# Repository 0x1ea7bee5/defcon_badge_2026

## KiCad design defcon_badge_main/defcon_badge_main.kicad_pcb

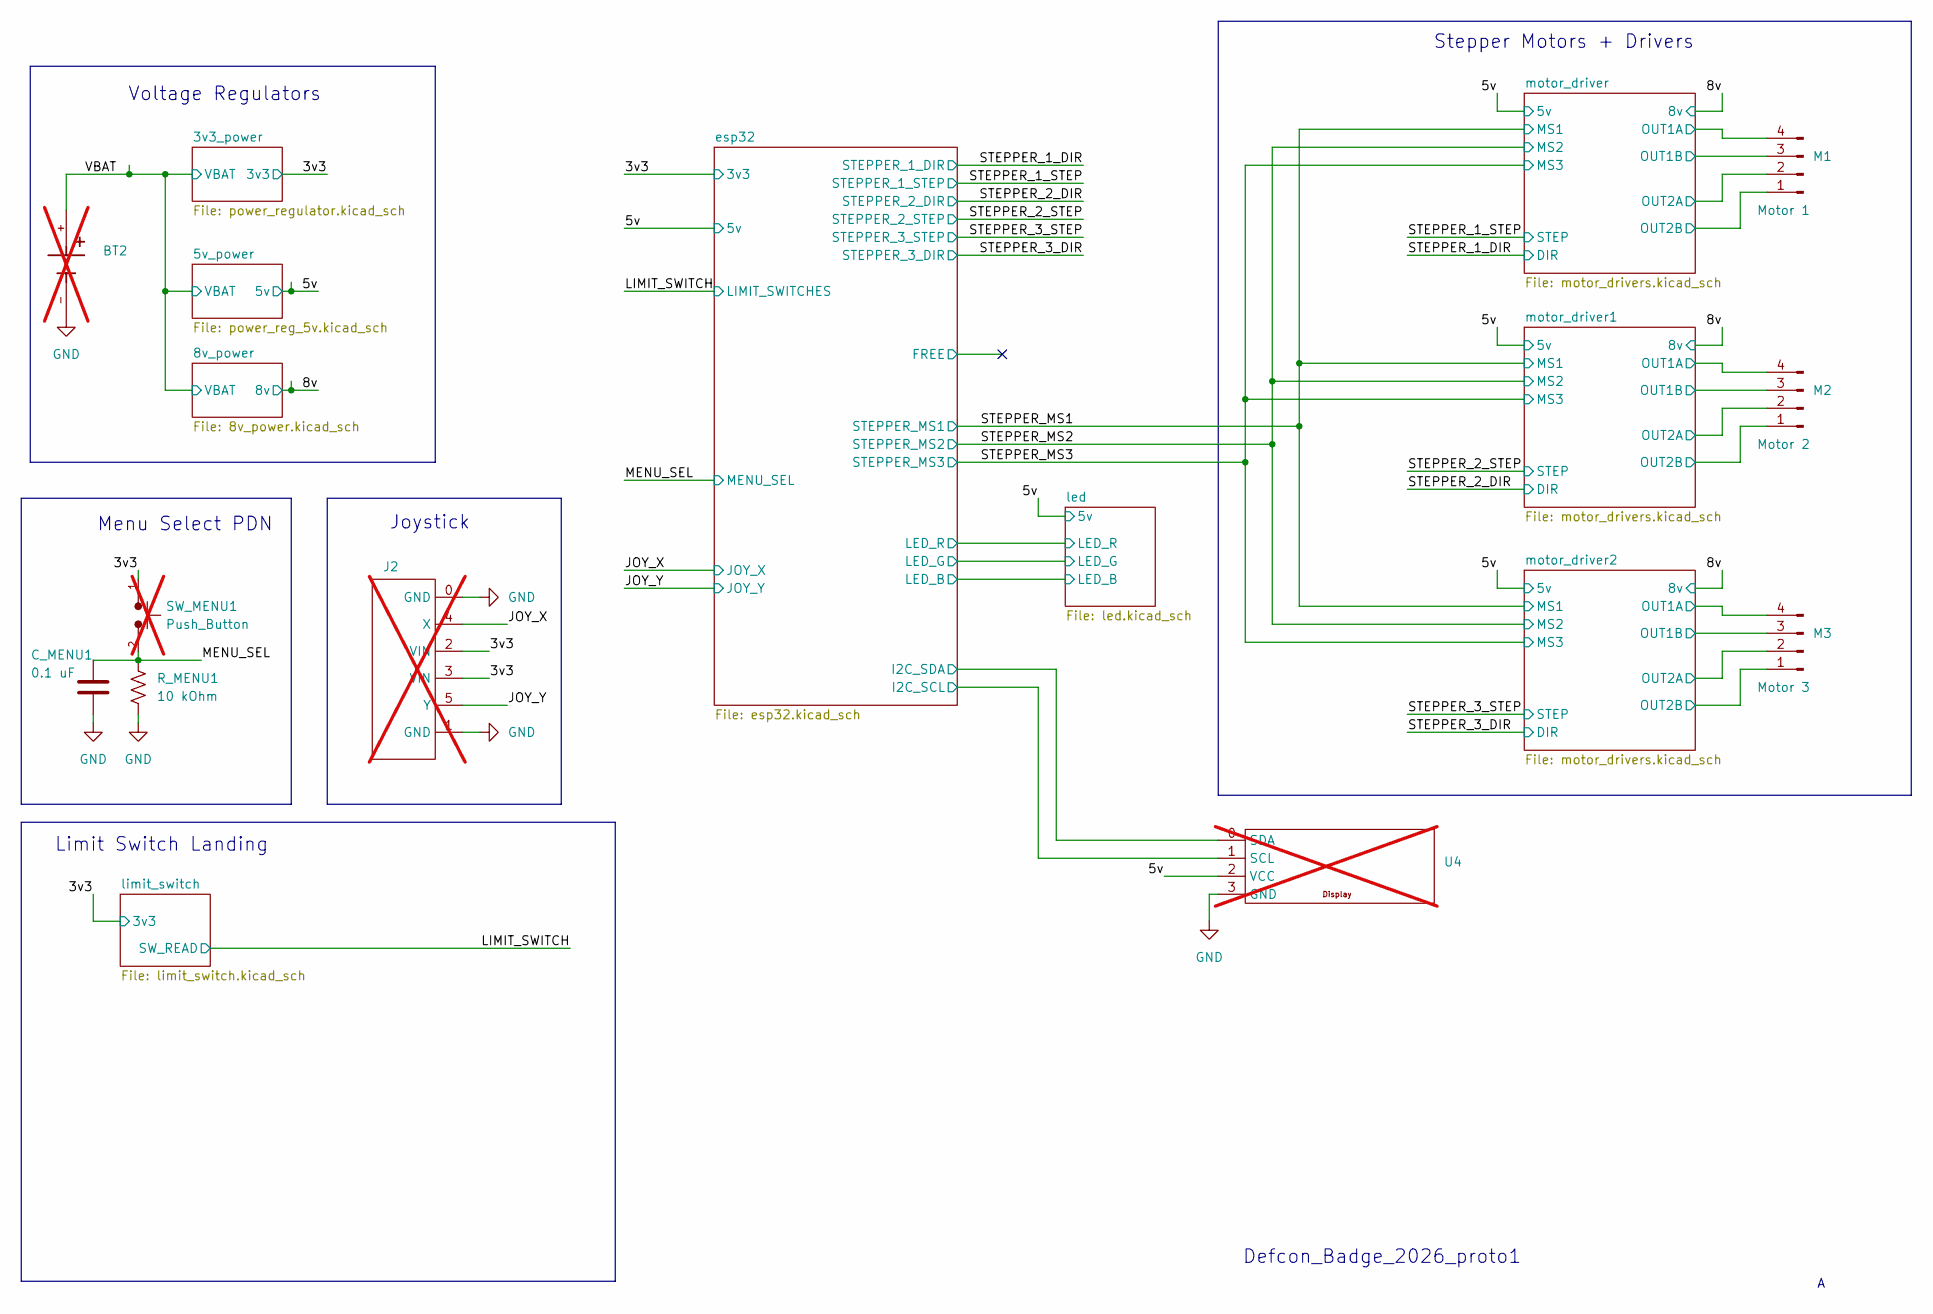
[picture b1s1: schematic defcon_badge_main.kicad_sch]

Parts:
BT2: BK-18650-PC2; BAT_BK-18650-PC2; PARTREV F; not fitted
C_MENU1: 0.1 uF; R_0402_1005Metric_Pad0.72x0.64mm_HandSolder_MINE; Rating 16V; MPN GMC10X7R104M16NTD
J2: joystick; not fitted
M1: Motor 1; motor_pins
M2: Motor 2; motor_pins
M3: Motor 3; motor_pins
R_MENU1: 10 kOhm; R_0805_2012Metric_Pad1.20x1.40mm_HandSolder_MINE; MPN RM10F1002CT
SW_MENU1: Push_Button; SW_SPST_PTS645; not fitted
U4: display; not fitted

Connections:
/3v3: J2.2 (VIN), J2.3 (VIN), SW_MENU1.1; also elsewhere on the board
/5v: U4.2 (VCC); also elsewhere on the board
/JOY_X: J2.4 (X); also elsewhere on the board
/JOY_Y: J2.5 (Y); also elsewhere on the board
/MENU_SEL: C_MENU1.2, R_MENU1.1, SW_MENU1.2; also elsewhere on the board
/VBAT: BT2.+; also elsewhere on the board
/esp32/I2C_SCL: U4.1 (SCL); also elsewhere on the board
/esp32/I2C_SDA: U4.0 (SDA); also elsewhere on the board
/motor_driver1/OUT1A: M2.4; also elsewhere on the board
/motor_driver1/OUT1B: M2.3; also elsewhere on the board
/motor_driver1/OUT2A: M2.2; also elsewhere on the board
/motor_driver1/OUT2B: M2.1; also elsewhere on the board
/motor_driver2/OUT1A: M3.4; also elsewhere on the board
/motor_driver2/OUT1B: M3.3; also elsewhere on the board
/motor_driver2/OUT2A: M3.2; also elsewhere on the board
/motor_driver2/OUT2B: M3.1; also elsewhere on the board
/motor_driver/OUT1A: M1.4; also elsewhere on the board
/motor_driver/OUT1B: M1.3; also elsewhere on the board
/motor_driver/OUT2A: M1.2; also elsewhere on the board
/motor_driver/OUT2B: M1.1; also elsewhere on the board
GND: BT2.-, C_MENU1.1, J2.0 (GND), J2.1 (GND), R_MENU1.2, U4.3 (GND); also elsewhere on the board

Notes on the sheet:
Stepper Motors + Drivers
Defcon_Badge_2026_proto1
Voltage Regulators
Joystick
Menu Select PDN
Limit Switch Landing

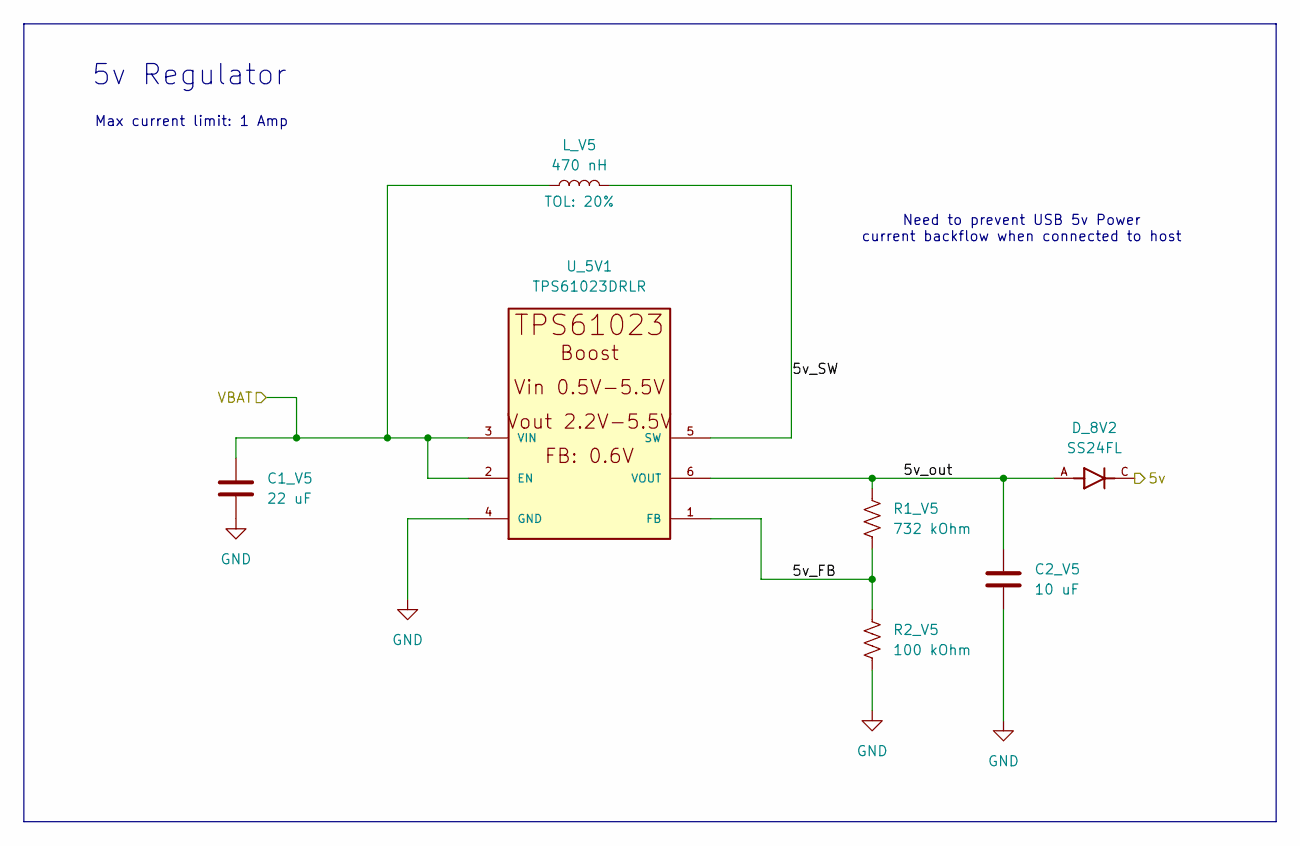
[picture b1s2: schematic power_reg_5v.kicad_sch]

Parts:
C1_V5: 22 uF; R_0805_2012Metric_Pad1.20x1.40mm_HandSolder_MINE; Rating 16V; MPN GMC21X5R226K16NT
C2_V5: 10 uF; R_0805_2012Metric_Pad1.20x1.40mm_HandSolder_MINE; Rating 16V; MPN GMC21X5R106K16NT
D_8V2: SS24FL; SODFL3617X108N; PARTREV A
L_V5: 470 nH; L_Neosid_SMS-ME3010; MPN 74479288147
R1_V5: 732 kOhm; R_1206_3216Metric_Pad1.30x1.75mm_HandSolder_MINE; MPN RM12F7323CT
R2_V5: 100 kOhm; R_1206_3216Metric_Pad1.30x1.75mm_HandSolder_MINE; MPN RM12F1003CT
U_5V1: TPS61023DRLR; SOT563-ORI; MPN TPS61023DRLR

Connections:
/5v: D_8V2.C; also elsewhere on the board
/5v_power/5v_FB: R1_V5.2, R2_V5.1, U_5V1.1 (FB)
/5v_power/5v_SW: L_V5.2, U_5V1.5 (SW)
/5v_power/5v_out: C2_V5.1, D_8V2.A, R1_V5.1, U_5V1.6 (VOUT)
/VBAT: C1_V5.1, L_V5.1, U_5V1.2 (EN), U_5V1.3 (VIN); also elsewhere on the board
GND: C1_V5.2, C2_V5.2, R2_V5.2, U_5V1.4 (GND); also elsewhere on the board

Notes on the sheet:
Max current limit: 1 Amp
Need to prevent USB 5v Power current backflow when connected to host
5v Regulator

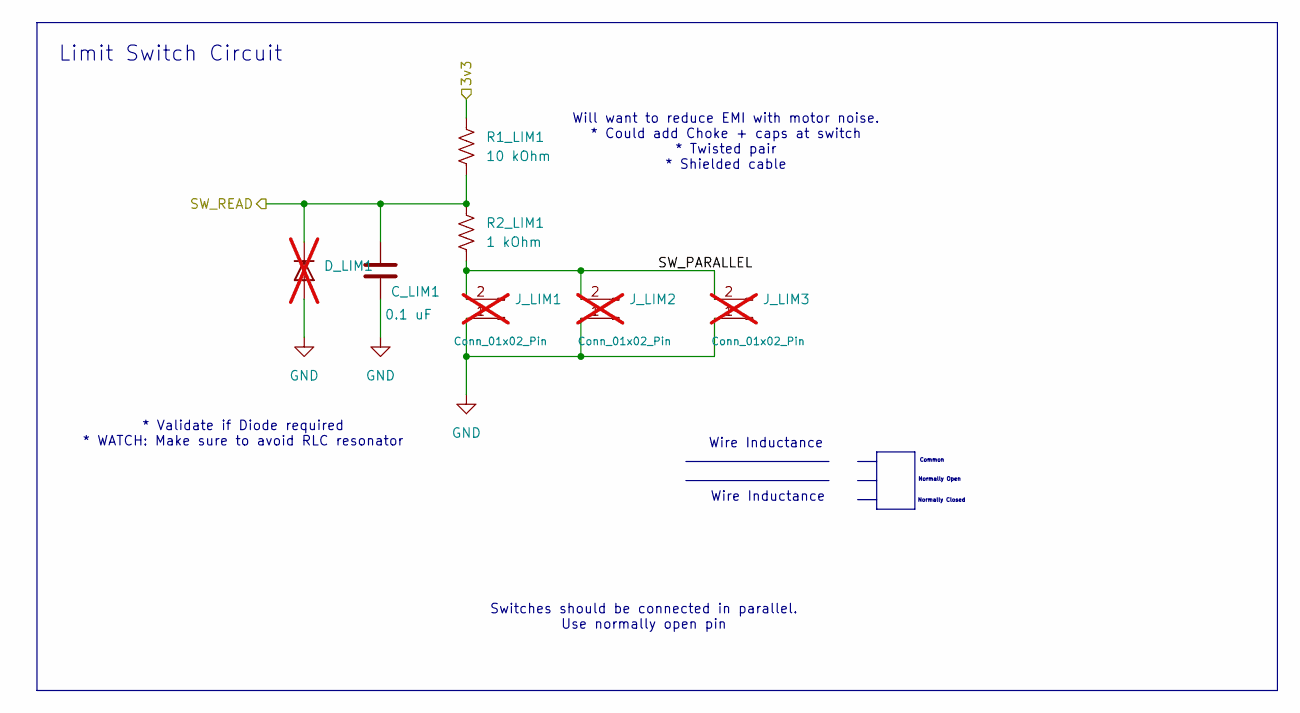
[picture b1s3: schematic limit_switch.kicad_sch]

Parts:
C_LIM1: 0.1 uF; R_0603_1608Metric_Pad0.98x0.95mm_HandSolder_MINE; Rating 16V; MPN GMC10X7R104M16NTD
D_LIM1: SOD-123; MPN 1N4148W-TP; not fitted
J_LIM1, J_LIM2, J_LIM3: Conn_01x02_Pin; pad_limit_switch; not fitted
R1_LIM1: 10 kOhm; R_0805_2012Metric_Pad1.20x1.40mm_HandSolder_MINE; MPN RM10F1002CT
R2_LIM1: 1 kOhm; R_1206_3216Metric_Pad1.30x1.75mm_HandSolder_MINE; MPN RMCS1206JT1K00

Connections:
/3v3: R1_LIM1.1; also elsewhere on the board
/LIMIT_SWITCH: C_LIM1.2, D_LIM1.1 (K), R1_LIM1.2, R2_LIM1.1; also elsewhere on the board
/limit_switch/SW_PARALLEL: J_LIM1.2, J_LIM2.2, J_LIM3.2, R2_LIM1.2
GND: C_LIM1.1, D_LIM1.2 (A), J_LIM1.1, J_LIM2.1, J_LIM3.1; also elsewhere on the board

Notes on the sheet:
* Validate if Diode required * WATCH: Make sure to avoid RLC resonator
Wire Inductance
Common
Normally Closed
Will want to reduce EMI with motor noise. * Could add Choke + caps at switch * Twisted pair * Shielded cable
Switches should be connected in parallel. Use normally open pin
Normally Open
Limit Switch Circuit

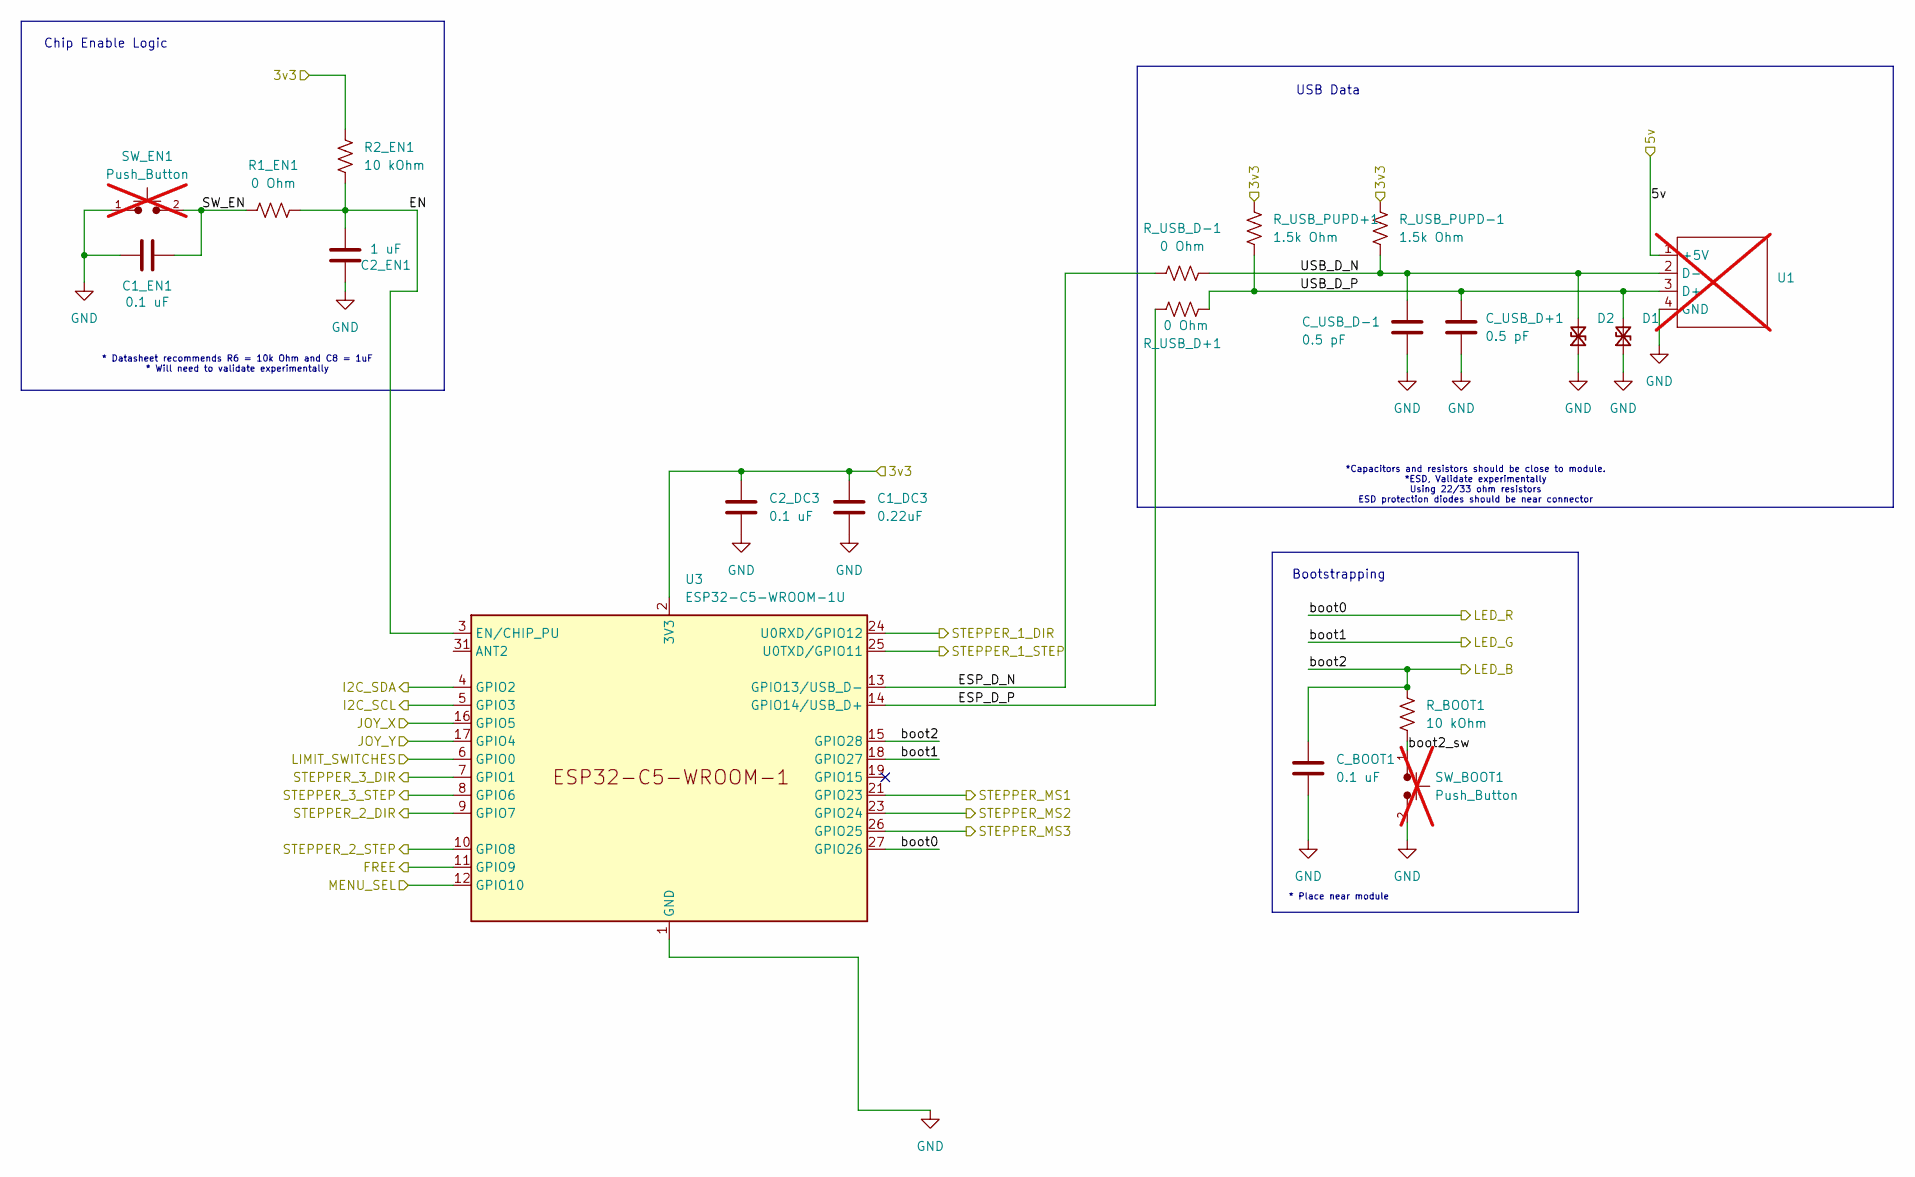
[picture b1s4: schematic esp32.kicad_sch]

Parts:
C1_DC3: 0.22uF; R_0805_2012Metric_Pad1.20x1.40mm_HandSolder_MINE; Rating 16V; MPN GMC10X5R224K25NT
C1_EN1, C2_DC3: 0.1 uF; R_0603_1608Metric_Pad0.98x0.95mm_HandSolder_MINE; Rating 16V; MPN GMC10X7R104M16NTD
C2_EN1: 1 uF; R_0805_2012Metric_Pad1.20x1.40mm_HandSolder_MINE; MPN GMC21X5R105K16NT
C_BOOT1: 0.1 uF; R_0603_1608Metric_Pad0.98x0.95mm_HandSolder_MINE; Rating 16V; MPN GMC10X7R104M16NTD
C_USB_D+1: 0.5 pF; R_0402_1005Metric_Pad0.72x0.64mm_HandSolder_MINE; Rating 16V; MPN GMC04CG0R5C50NT
C_USB_D-1: 0.5 pF; R_0402_1005Metric_Pad0.72x0.64mm_HandSolder_MINE; Rating 16V; MPN GMC04CG0R5C50NT
D1, D2: PESD0402; R_0402_1005Metric_Pad0.72x0.64mm_HandSolder_MINE; Rating 14VWM/40VC; MPN CES10402V05B0DG
R1_EN1: 0 Ohm; R_0603_1608Metric_Pad0.98x0.95mm_HandSolder_MINE; MPN RM06J000CT
R2_EN1: 10 kOhm; R_0805_2012Metric_Pad1.20x1.40mm_HandSolder_MINE; MPN RM10F1002CT
R_BOOT1: 10 kOhm; R_0805_2012Metric_Pad1.20x1.40mm_HandSolder_MINE; MPN RM10F1002CT
R_USB_D+1: 0 Ohm; R_0402_1005Metric_Pad0.72x0.64mm_HandSolder_MINE; MPN RM04J000CT
R_USB_D-1: 0 Ohm; R_0402_1005Metric_Pad0.72x0.64mm_HandSolder_MINE; MPN RM04J000CT
R_USB_PUPD+1: 1.5k Ohm; R_0402_1005Metric_Pad0.72x0.64mm_HandSolder_MINE; MPN RM04J152CT
R_USB_PUPD-1: 1.5k Ohm; R_0402_1005Metric_Pad0.72x0.64mm_HandSolder_MINE; MPN RM04J152CT
SW_BOOT1: Push_Button; SW_SPST_PTS810; not fitted
SW_EN1: Push_Button; SW_SPST_PTS810; not fitted
U1: usb_typea_boardedge; not fitted
U3: ESP32-C5-WROOM-1U; MPN ESP32-C5-WROOM-1U-N8R8

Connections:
/3v3: C1_DC3.1, C2_DC3.1, R2_EN1.2, R_USB_PUPD+1.2, R_USB_PUPD-1.2, U3.2 (3V3); also elsewhere on the board
/5v: U1.1 (+5V); also elsewhere on the board
/JOY_X: U3.16 (GPIO5); also elsewhere on the board
/JOY_Y: U3.17 (GPIO4); also elsewhere on the board
/LIMIT_SWITCH: U3.6 (GPIO0); also elsewhere on the board
/MENU_SEL: U3.12 (GPIO10); also elsewhere on the board
/STEPPER_1_DIR: U3.24 (U0RXD/GPIO12); also elsewhere on the board
/STEPPER_1_STEP: U3.25 (U0TXD/GPIO11); also elsewhere on the board
/STEPPER_2_DIR: U3.9 (GPIO7); also elsewhere on the board
/STEPPER_2_STEP: U3.10 (GPIO8); also elsewhere on the board
/STEPPER_3_DIR: U3.7 (GPIO1); also elsewhere on the board
/STEPPER_3_STEP: U3.8 (GPIO6); also elsewhere on the board
/STEPPER_MS1: U3.21 (GPIO23); also elsewhere on the board
/STEPPER_MS2: U3.23 (GPIO24); also elsewhere on the board
/STEPPER_MS3: U3.26 (GPIO25); also elsewhere on the board
/esp32/EN: C2_EN1.1, R1_EN1.2, R2_EN1.1, U3.3 (EN/CHIP_PU)
/esp32/ESP_D_N: R_USB_D-1.1, U3.13 (GPIO13/USB_D-)
/esp32/ESP_D_P: R_USB_D+1.2, U3.14 (GPIO14/USB_D+)
/esp32/FREE: U3.11 (GPIO9)
/esp32/I2C_SCL: U3.5 (GPIO3); also elsewhere on the board
/esp32/I2C_SDA: U3.4 (GPIO2); also elsewhere on the board
/esp32/SW_EN: C1_EN1.1, R1_EN1.1, SW_EN1.2
/esp32/USB_D_N: C_USB_D-1.1, D2.2 (A2), R_USB_D-1.2, R_USB_PUPD-1.1, U1.2 (D-)
/esp32/USB_D_P: C_USB_D+1.1, D1.2 (A2), R_USB_D+1.1, R_USB_PUPD+1.1, U1.3 (D+)
/esp32/boot0: U3.27 (GPIO26); also elsewhere on the board
/esp32/boot1: U3.18 (GPIO27); also elsewhere on the board
/esp32/boot2: C_BOOT1.1, R_BOOT1.2, U3.15 (GPIO28); also elsewhere on the board
/esp32/boot2_sw: R_BOOT1.1, SW_BOOT1.1
GND: C1_DC3.2, C1_EN1.2, C2_DC3.2, C2_EN1.2, C_BOOT1.2, C_USB_D+1.2, C_USB_D-1.2, D1.1 (A1), D2.1 (A1), SW_BOOT1.2, SW_EN1.1, U1.4 (GND), U3.1 (GND), U3.28 (GND), U3.29 (GND), U3.30 (GND), U3.32 (GND); also elsewhere on the board

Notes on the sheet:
Chip Enable Logic
USB Data
* Place near module
* Datasheet recommends R6 = 10k Ohm and C8 = 1uF * Will need to validate experimentally
*Capacitors and resistors should be close to module. *ESD, Validate experimentally Using 22/33 ohm resistors ESD protection diodes should be near connector
Bootstrapping

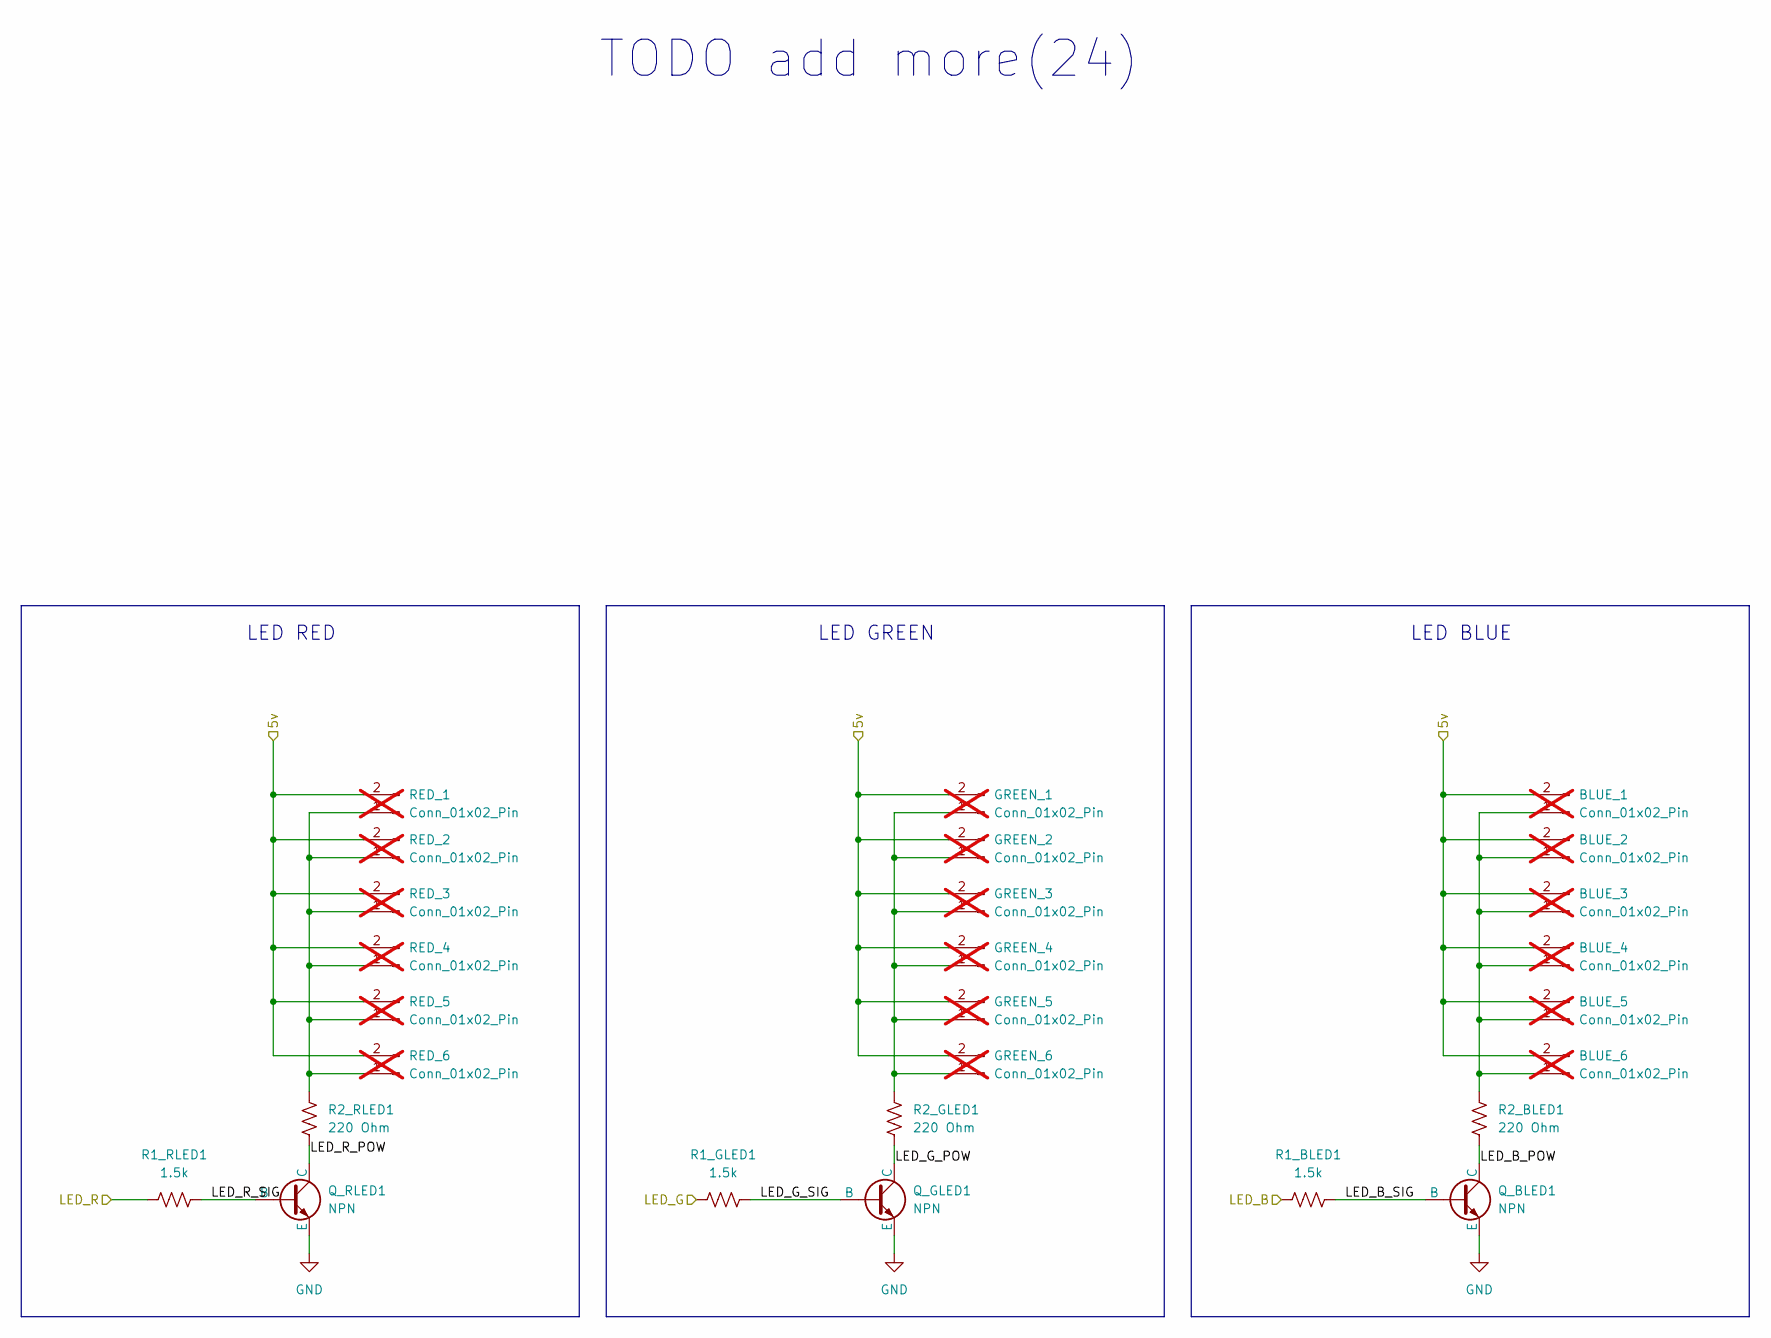
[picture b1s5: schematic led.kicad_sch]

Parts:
BLUE_1, BLUE_2, BLUE_3, BLUE_4, BLUE_5, BLUE_6: Conn_01x02_Pin; PinHeader_1x02_P1.00mm_Vertical; not fitted
GREEN_1, GREEN_2, GREEN_3, GREEN_4, GREEN_5, GREEN_6: Conn_01x02_Pin; PinHeader_1x02_P1.00mm_Vertical; not fitted
Q_BLED1: NPN; SOT-23-3; MPN MMUN2211LT1G
Q_GLED1: NPN; SOT-23-3; MPN MMUN2211LT1G
Q_RLED1: NPN; SOT-23-3; MPN MMUN2211LT1G
R1_BLED1, R1_GLED1, R1_RLED1: 1.5k; R_0805_2012Metric_Pad1.20x1.40mm_HandSolder; MPN RM10F1501CT
R2_BLED1, R2_GLED1, R2_RLED1: 220 Ohm; R_0805_2012Metric_Pad1.20x1.40mm_HandSolder; MPN RM10F2200CT
RED_1, RED_2, RED_3, RED_4, RED_5, RED_6: Conn_01x02_Pin; PinHeader_1x02_P1.00mm_Vertical; not fitted

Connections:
/5v: BLUE_1.2, BLUE_2.2, BLUE_3.2, BLUE_4.2, BLUE_5.2, BLUE_6.2, GREEN_1.2, GREEN_2.2, GREEN_3.2, GREEN_4.2, GREEN_5.2, GREEN_6.2, RED_1.2, RED_2.2, RED_3.2, RED_4.2, RED_5.2, RED_6.2; also elsewhere on the board
/esp32/boot0: R1_RLED1.1; also elsewhere on the board
/esp32/boot1: R1_GLED1.1; also elsewhere on the board
/esp32/boot2: R1_BLED1.1; also elsewhere on the board
/led/LED_B_POW: Q_BLED1.1 (C), R2_BLED1.2
/led/LED_B_SIG: Q_BLED1.2 (B), R1_BLED1.2
/led/LED_G_POW: Q_GLED1.1 (C), R2_GLED1.2
/led/LED_G_SIG: Q_GLED1.2 (B), R1_GLED1.2
/led/LED_R_POW: Q_RLED1.1 (C), R2_RLED1.2
/led/LED_R_SIG: Q_RLED1.2 (B), R1_RLED1.2
GND: Q_BLED1.3 (E), Q_GLED1.3 (E), Q_RLED1.3 (E); also elsewhere on the board
unnamed: BLUE_1.1, BLUE_2.1, BLUE_3.1, BLUE_4.1, BLUE_5.1, BLUE_6.1, R2_BLED1.1
unnamed: GREEN_1.1, GREEN_2.1, GREEN_3.1, GREEN_4.1, GREEN_5.1, GREEN_6.1, R2_GLED1.1
unnamed: R2_RLED1.1, RED_1.1, RED_2.1, RED_3.1, RED_4.1, RED_5.1, RED_6.1

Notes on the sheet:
TODO add more(24)
LED RED
LED BLUE
LED GREEN

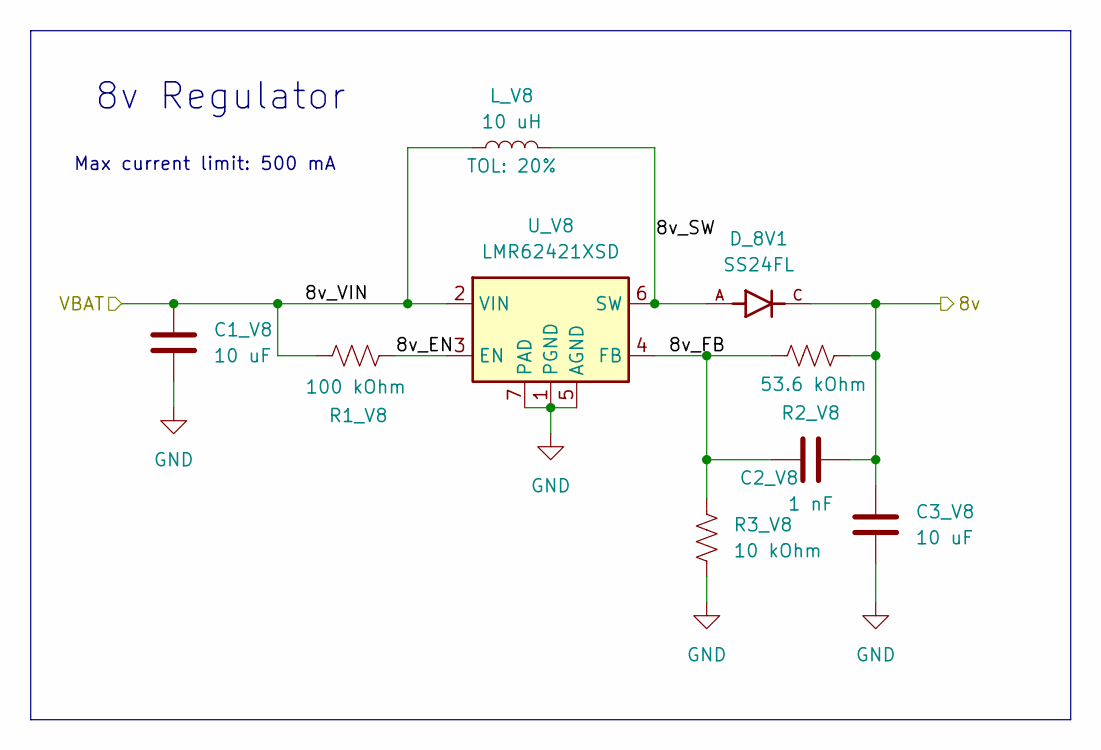
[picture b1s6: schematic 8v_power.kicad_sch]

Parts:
C1_V8, C3_V8: 10 uF; R_0805_2012Metric_Pad1.20x1.40mm_HandSolder_MINE; Rating 16V; MPN GMC21X5R106K16NT
C2_V8: 1 nF; R_0603_1608Metric_Pad0.98x0.95mm_HandSolder_MINE; MPN GMC10X7R102K16NT
D_8V1: SS24FL; SODFL3617X108N; PARTREV A
L_V8: 10 uH; 0_1uh; MPN 74438357100
R1_V8: 100 kOhm; R_1206_3216Metric_Pad1.30x1.75mm_HandSolder_MINE; MPN RM12F1003CT
R2_V8: 53.6 kOhm; R_1206_3216Metric_Pad1.30x1.75mm_HandSolder_MINE; MPN RM12F5362CT
R3_V8: 10 kOhm; R_1206_3216Metric_Pad1.30x1.75mm_HandSolder_MINE; MPN RM12F1002CT
U_V8: LMR62421XSD; WSON-6-1EP_3x3mm_P0.95mm; MPN LMR62421XSD/NOPB

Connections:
/8v: C2_V8.2, C3_V8.1, D_8V1.C, R2_V8.1; also elsewhere on the board
/8v_power/8v_EN: R1_V8.1, U_V8.3 (EN)
/8v_power/8v_FB: C2_V8.1, R2_V8.2, R3_V8.2, U_V8.4 (FB)
/8v_power/8v_SW: D_8V1.A, L_V8.2, U_V8.6 (SW)
/VBAT: C1_V8.1, L_V8.1, R1_V8.2, U_V8.2 (VIN); also elsewhere on the board
GND: C1_V8.2, C3_V8.2, R3_V8.1, U_V8.1 (PGND), U_V8.5 (AGND), U_V8.7 (PAD); also elsewhere on the board

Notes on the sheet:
Max current limit: 500 mA
8v Regulator

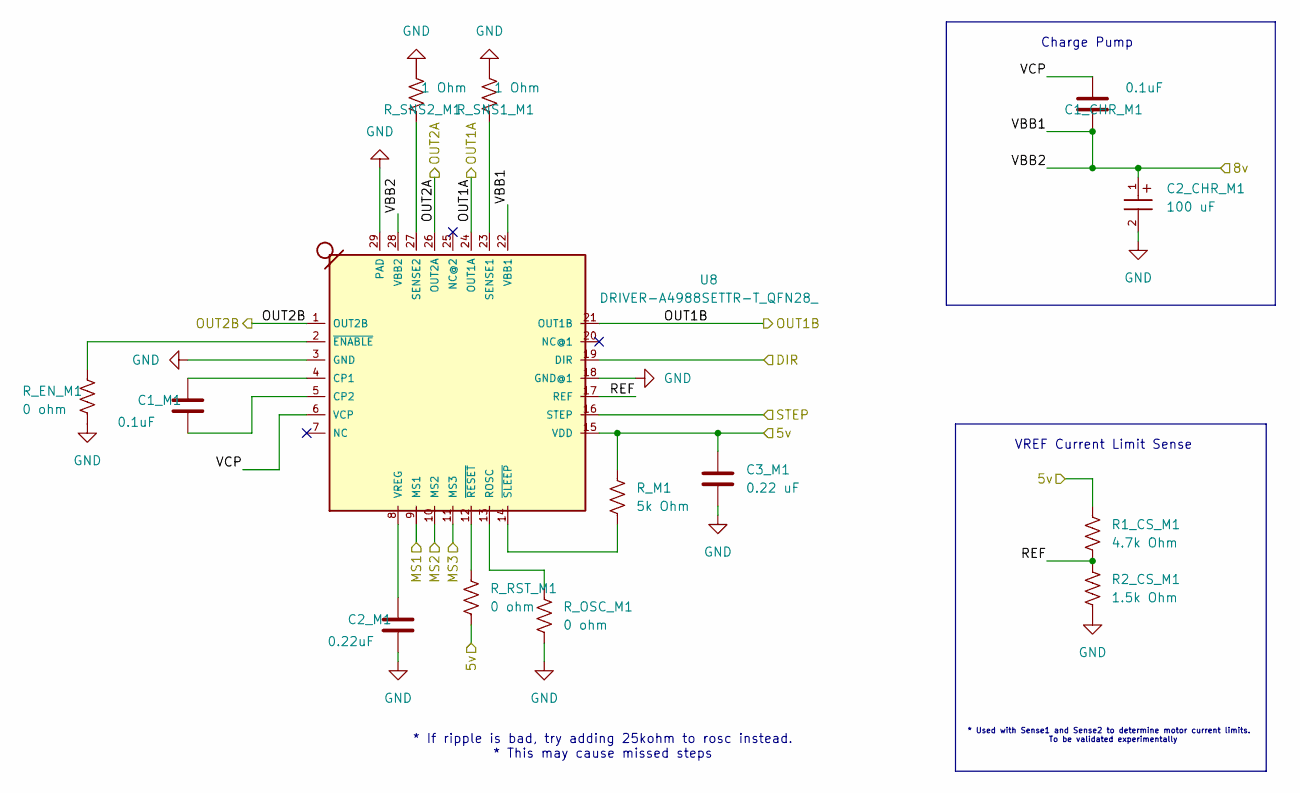
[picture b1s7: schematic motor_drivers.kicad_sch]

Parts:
C1_CHR_M1, C1_M1: 0.1uF; R_0603_1608Metric_Pad0.98x0.95mm_HandSolder_MINE; Rating 16V; MPN GMC10X7R104M16NTD
C2_CHR_M1: 100 uF; WCAP-ASLI_6.3X5.5_DXL_; MPN 865080343009
C2_M1: 0.22uF; R_0603_1608Metric_Pad0.98x0.95mm_HandSolder_MINE; Rating 16V; MPN GMC10X5R224K25NT
C3_M1: 0.22 uF; R_0603_1608Metric_Pad0.98x0.95mm_HandSolder_MINE; Rating 16V; MPN GMC10X5R224K25NT
R1_CS_M1: 4.7k Ohm; R_0603_1608Metric_Pad0.98x0.95mm_HandSolder_MINE; MPN RM06J472CT
R2_CS_M1: 1.5k Ohm; R_0603_1608Metric_Pad0.98x0.95mm_HandSolder_MINE; MPN RM06F1501CT
R_EN_M1: 0 ohm; R_0603_1608Metric_Pad0.98x0.95mm_HandSolder_MINE; MPN RM06J000CT
R_M1: 5k Ohm; R_0603_1608Metric_Pad0.98x0.95mm_HandSolder_MINE; MPN MCT06030D5001BP500
R_OSC_M1: 0 ohm; R_0603_1608Metric_Pad0.98x0.95mm_HandSolder_MINE; MPN RM06J000CT
R_RST_M1: 0 ohm; R_0603_1608Metric_Pad0.98x0.95mm_HandSolder_MINE; MPN RM06J000CT
R_SNS1_M1, R_SNS2_M1: 1 Ohm; R_0603_1608Metric_Pad0.98x0.95mm_HandSolder_MINE; MPN RM06J1R0CT
U8: DRIVER-A4988SETTR-T_QFN28_; QFN28G_0.5-5X5MM; MPN A4988SETTR-T

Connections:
/5v: C3_M1.1, R1_CS_M1.1, R_M1.1, R_RST_M1.2, U8.15 (VDD); also elsewhere on the board
/8v: C1_CHR_M1.2, C2_CHR_M1.1, U8.22 (VBB1), U8.28 (VBB2); also elsewhere on the board
/STEPPER_1_DIR: U8.19 (DIR); also elsewhere on the board
/STEPPER_1_STEP: U8.16 (STEP); also elsewhere on the board
/STEPPER_MS1: U8.9 (MS1); also elsewhere on the board
/STEPPER_MS2: U8.10 (MS2); also elsewhere on the board
/STEPPER_MS3: U8.11 (MS3); also elsewhere on the board
/motor_driver/OUT1A: U8.24 (OUT1A); also elsewhere on the board
/motor_driver/OUT1B: U8.21 (OUT1B); also elsewhere on the board
/motor_driver/OUT2A: U8.26 (OUT2A); also elsewhere on the board
/motor_driver/OUT2B: U8.1 (OUT2B); also elsewhere on the board
/motor_driver/REF: R1_CS_M1.2, R2_CS_M1.1, U8.17 (REF)
/motor_driver/VCP: C1_CHR_M1.1, U8.6 (VCP)
GND: C2_CHR_M1.2, C2_M1.1, C3_M1.2, R2_CS_M1.2, R_EN_M1.2, R_OSC_M1.2, R_SNS1_M1.2, R_SNS2_M1.2, U8.3 (GND), U8.18 (GND@1), U8.29 (PAD); also elsewhere on the board
unnamed: C1_M1.2, U8.4 (CP1)
unnamed: C1_M1.1, U8.5 (CP2)
unnamed: R_OSC_M1.1, U8.13 (ROSC)
unnamed: R_SNS1_M1.1, U8.23 (SENSE1)
unnamed: R_SNS2_M1.1, U8.27 (SENSE2)
unnamed: C2_M1.2, U8.8 (VREG)
unnamed: R_EN_M1.1, U8.2 (~ENABLE)
unnamed: R_RST_M1.1, U8.12 (~RESET)
unnamed: R_M1.2, U8.14 (~SLEEP)

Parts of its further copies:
C1_CHR_M2, C1_CHR_M3, C1_M2, C1_M3: 0.1uF; R_0603_1608Metric_Pad0.98x0.95mm_HandSolder_MINE; Rating 16V; MPN GMC10X7R104M16NTD
C2_CHR_M2, C2_CHR_M3: 100 uF; WCAP-ASLI_6.3X5.5_DXL_; MPN 865080343009
C2_M2, C2_M3: 0.22uF; R_0603_1608Metric_Pad0.98x0.95mm_HandSolder_MINE; Rating 16V; MPN GMC10X5R224K25NT
C3_M2, C3_M3: 0.22 uF; R_0603_1608Metric_Pad0.98x0.95mm_HandSolder_MINE; Rating 16V; MPN GMC10X5R224K25NT
R1_CS_M2, R1_CS_M3: 4.7k Ohm; R_0603_1608Metric_Pad0.98x0.95mm_HandSolder_MINE; MPN RM06J472CT
R2_CS_M2, R2_CS_M3: 1.5k Ohm; R_0603_1608Metric_Pad0.98x0.95mm_HandSolder_MINE; MPN RM06F1501CT
R_EN_M2, R_EN_M3: 0 ohm; R_0603_1608Metric_Pad0.98x0.95mm_HandSolder_MINE; MPN RM06J000CT
R_M2, R_M3: 5k Ohm; R_0603_1608Metric_Pad0.98x0.95mm_HandSolder_MINE; MPN MCT06030D5001BP500
R_OSC_M2, R_OSC_M3: 0 ohm; R_0603_1608Metric_Pad0.98x0.95mm_HandSolder_MINE; MPN RM06J000CT
R_RST_M2, R_RST_M3: 0 ohm; R_0603_1608Metric_Pad0.98x0.95mm_HandSolder_MINE; MPN RM06J000CT
R_SNS1_M2, R_SNS1_M3, R_SNS2_M2, R_SNS2_M3: 1 Ohm; R_0603_1608Metric_Pad0.98x0.95mm_HandSolder_MINE; MPN RM06J1R0CT
U5, U6: DRIVER-A4988SETTR-T_QFN28_; QFN28G_0.5-5X5MM; MPN A4988SETTR-T

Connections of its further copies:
/5v: C3_M2.1, C3_M3.1, R1_CS_M2.1, R1_CS_M3.1, R_M2.1, R_M3.1, R_RST_M2.2, R_RST_M3.2, U5.15 (VDD), U6.15 (VDD); also elsewhere on the board
/8v: C1_CHR_M2.2, C1_CHR_M3.2, C2_CHR_M2.1, C2_CHR_M3.1, U5.22 (VBB1), U5.28 (VBB2), U6.22 (VBB1), U6.28 (VBB2); also elsewhere on the board
/STEPPER_2_DIR: U5.19 (DIR); also elsewhere on the board
/STEPPER_2_STEP: U5.16 (STEP); also elsewhere on the board
/STEPPER_3_DIR: U6.19 (DIR); also elsewhere on the board
/STEPPER_3_STEP: U6.16 (STEP); also elsewhere on the board
/STEPPER_MS1: U5.9 (MS1), U6.9 (MS1); also elsewhere on the board
/STEPPER_MS2: U5.10 (MS2), U6.10 (MS2); also elsewhere on the board
/STEPPER_MS3: U5.11 (MS3), U6.11 (MS3); also elsewhere on the board
/motor_driver1/OUT1A: U5.24 (OUT1A); also elsewhere on the board
/motor_driver1/OUT1B: U5.21 (OUT1B); also elsewhere on the board
/motor_driver1/OUT2A: U5.26 (OUT2A); also elsewhere on the board
/motor_driver1/OUT2B: U5.1 (OUT2B); also elsewhere on the board
/motor_driver1/REF: R1_CS_M2.2, R2_CS_M2.1, U5.17 (REF)
/motor_driver1/VCP: C1_CHR_M2.1, U5.6 (VCP)
/motor_driver2/OUT1A: U6.24 (OUT1A); also elsewhere on the board
/motor_driver2/OUT1B: U6.21 (OUT1B); also elsewhere on the board
/motor_driver2/OUT2A: U6.26 (OUT2A); also elsewhere on the board
/motor_driver2/OUT2B: U6.1 (OUT2B); also elsewhere on the board
/motor_driver2/REF: R1_CS_M3.2, R2_CS_M3.1, U6.17 (REF)
/motor_driver2/VCP: C1_CHR_M3.1, U6.6 (VCP)
GND: C2_CHR_M2.2, C2_CHR_M3.2, C2_M2.1, C2_M3.1, C3_M2.2, C3_M3.2, R2_CS_M2.2, R2_CS_M3.2, R_EN_M2.2, R_EN_M3.2, R_OSC_M2.2, R_OSC_M3.2, R_SNS1_M2.2, R_SNS1_M3.2, R_SNS2_M2.2, R_SNS2_M3.2, U5.3 (GND), U5.18 (GND@1), U5.29 (PAD), U6.3 (GND), U6.18 (GND@1), U6.29 (PAD); also elsewhere on the board
unnamed: C1_M2.2, U5.4 (CP1)
unnamed: C1_M2.1, U5.5 (CP2)
unnamed: R_OSC_M2.1, U5.13 (ROSC)
unnamed: R_SNS1_M2.1, U5.23 (SENSE1)
unnamed: R_SNS2_M2.1, U5.27 (SENSE2)
unnamed: C2_M2.2, U5.8 (VREG)
unnamed: R_EN_M2.1, U5.2 (~ENABLE)
unnamed: R_RST_M2.1, U5.12 (~RESET)
unnamed: R_M2.2, U5.14 (~SLEEP)
unnamed: C1_M3.2, U6.4 (CP1)
unnamed: C1_M3.1, U6.5 (CP2)
unnamed: R_OSC_M3.1, U6.13 (ROSC)
unnamed: R_SNS1_M3.1, U6.23 (SENSE1)
unnamed: R_SNS2_M3.1, U6.27 (SENSE2)
unnamed: C2_M3.2, U6.8 (VREG)
unnamed: R_EN_M3.1, U6.2 (~ENABLE)
unnamed: R_RST_M3.1, U6.12 (~RESET)
unnamed: R_M3.2, U6.14 (~SLEEP)

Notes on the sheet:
* Used with Sense1 and Sense2 to determine motor current limits. To be validated experimentally
VREF Current Limit Sense
Charge Pump
* If ripple is bad, try adding 25kohm to rosc instead. * This may cause missed steps

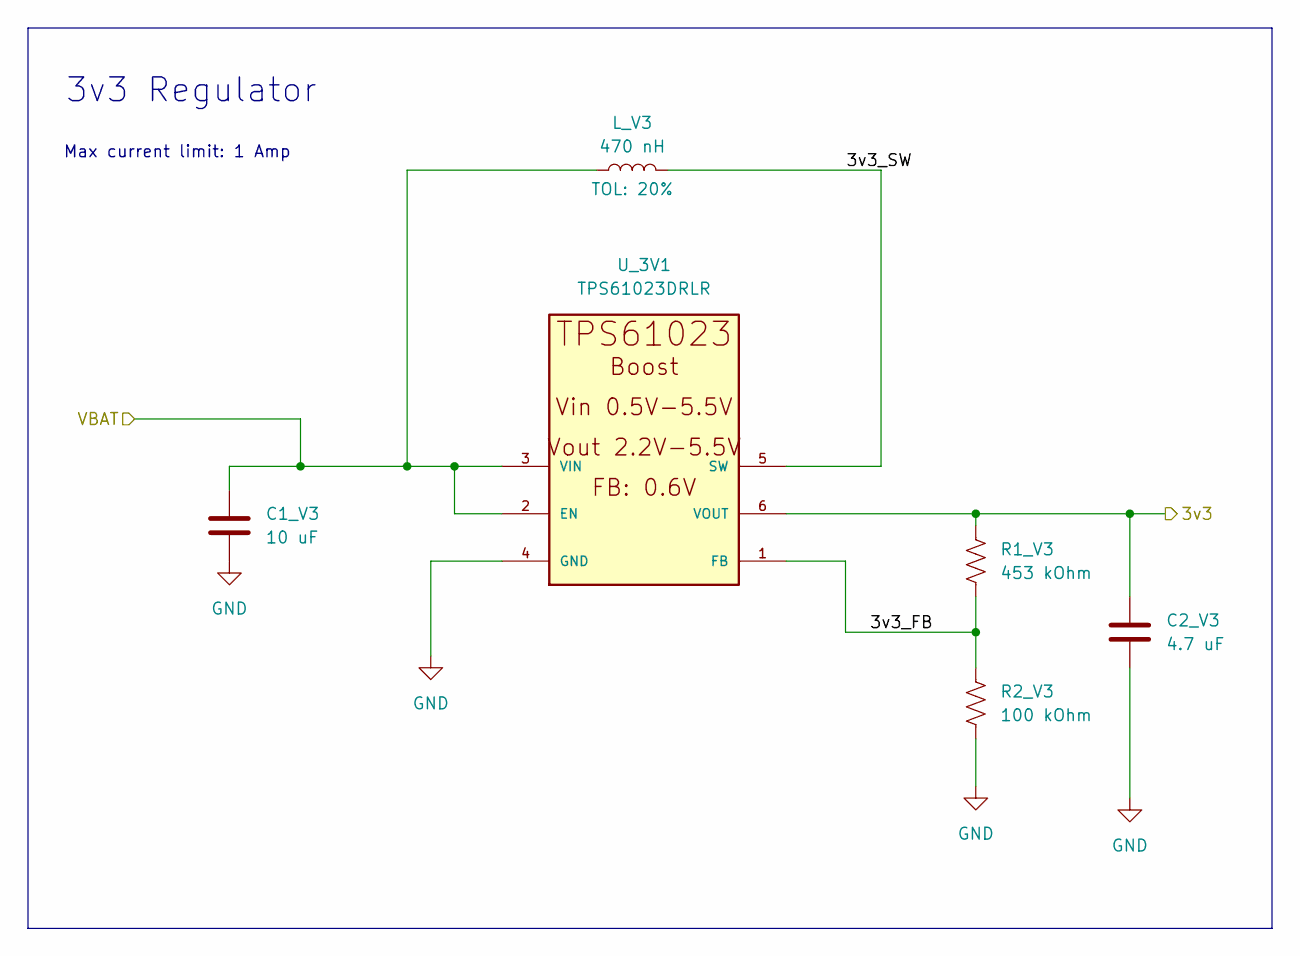
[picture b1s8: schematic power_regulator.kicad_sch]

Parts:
C1_V3: 10 uF; R_0805_2012Metric_Pad1.20x1.40mm_HandSolder_MINE; Rating 16V; MPN GMC21X5R106K16NT
C2_V3: 4.7 uF; R_0805_2012Metric_Pad1.20x1.40mm_HandSolder_MINE; Rating 16V; MPN GMC10Y5V475Z6R3NT
L_V3: 470 nH; L_Neosid_SMS-ME3010; MPN 74479288147
R1_V3: 453 kOhm; R_1206_3216Metric_Pad1.30x1.75mm_HandSolder_MINE; MPN RM12F4533CT
R2_V3: 100 kOhm; R_1206_3216Metric_Pad1.30x1.75mm_HandSolder_MINE; MPN RM12F1003CT
U_3V1: TPS61023DRLR; SOT563-ORI; MPN TPS61023DRLR

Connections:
/3v3: C2_V3.1, R1_V3.1, U_3V1.6 (VOUT); also elsewhere on the board
/3v3_power/3v3_FB: R1_V3.2, R2_V3.1, U_3V1.1 (FB)
/3v3_power/3v3_SW: L_V3.2, U_3V1.5 (SW)
/VBAT: C1_V3.1, L_V3.1, U_3V1.2 (EN), U_3V1.3 (VIN); also elsewhere on the board
GND: C1_V3.2, C2_V3.2, R2_V3.2, U_3V1.4 (GND); also elsewhere on the board

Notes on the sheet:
Max current limit: 1 Amp
3v3 Regulator
